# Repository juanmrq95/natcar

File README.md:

# Sp17_team3
Andrew Chan, Neeli Tummala, Juan Rodriguez

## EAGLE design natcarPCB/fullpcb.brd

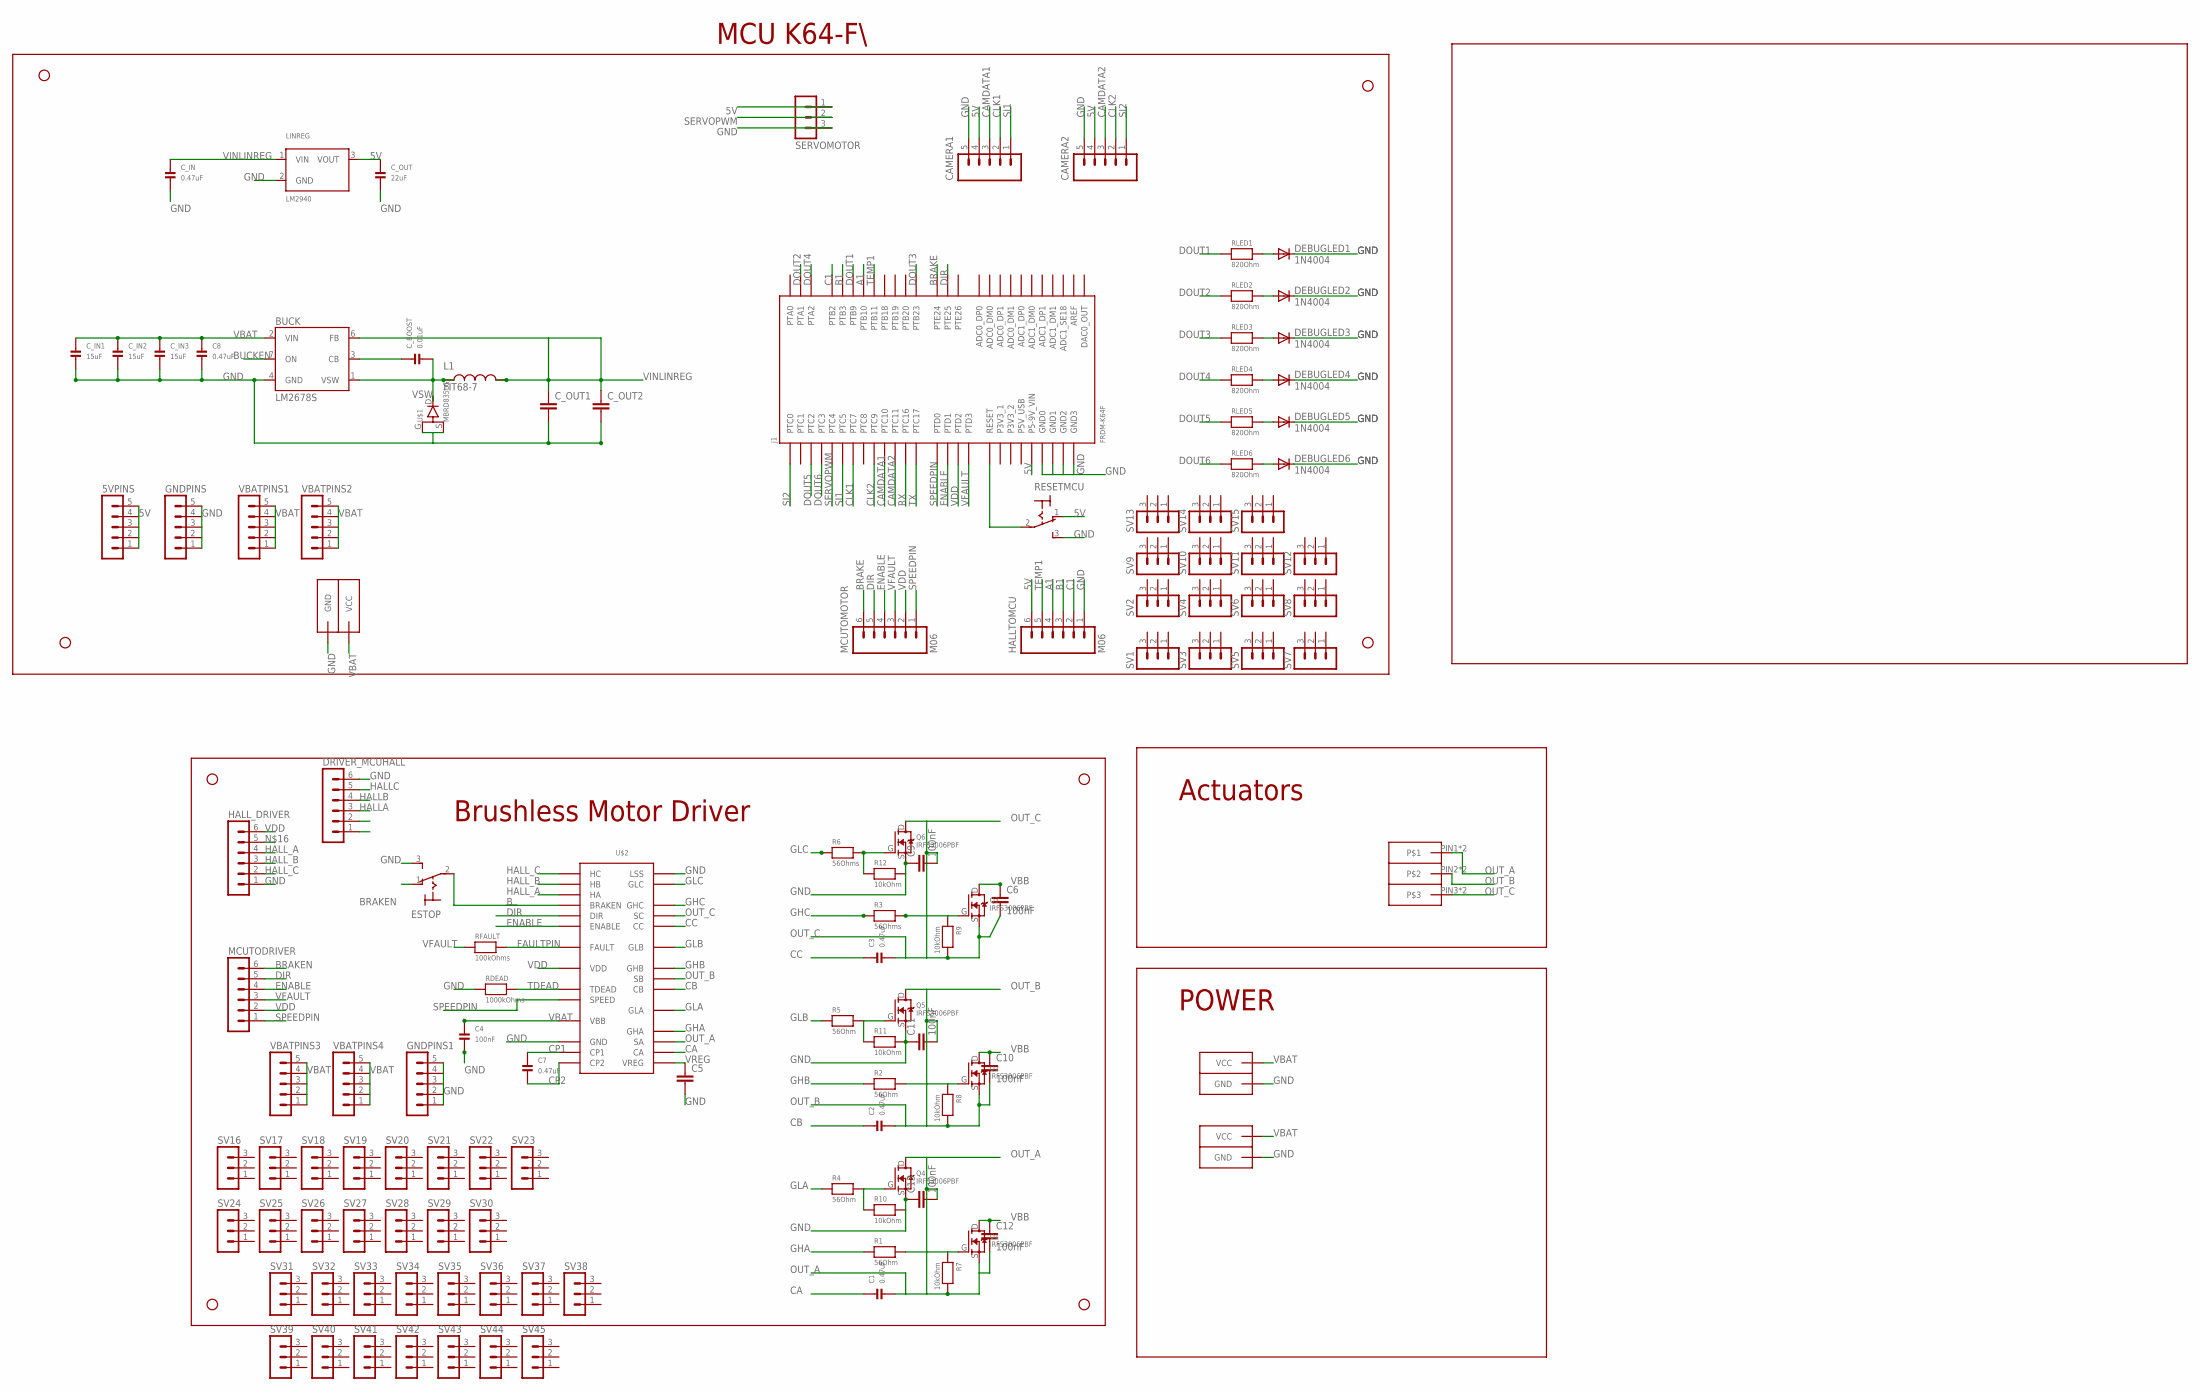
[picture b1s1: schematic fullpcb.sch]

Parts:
5VPINS: MA05-1
BOARD2BOARD: ANDERSON_PP_DOUBLEHORIZONTAL; ANDERSON_PP_DOUB_HORZ
BUCK: LM2678S; TO263-7
C1, C2, C3, C7, C8: 0.47uF; 0805
C4: 100nF; 0805
C5: C2,5-3; C2.5-3
C6, C9, C10, C11, C12, C13: 100nF; C2.5-3
CAMERA1, CAMERA2: M05PTH; 1X05
CONN1, CONN2: ANDERSON_PP_DOUBLEHORIZONTAL; ANDERSON_PP_DOUB_HORZ
CONN3: ANDERSON_PP_TRIPHORIZ; ANDERSON_PP_TRIP_HORZ
C_BOOST: 0.01uF; 0805
C_IN: 0.47uF; 0805
C_IN1, C_IN2, C_IN3: 15uF; 0805
C_OUT: 22uF; 0805
C_OUT1, C_OUT2: C2,5-3; C2.5-3
DEBUGLED1, DEBUGLED2, DEBUGLED3, DEBUGLED4, DEBUGLED5, DEBUGLED6: 1N4004; DO41-10
DRIVER_MCUHALL: MA06-1
ESTOP: M9040P
GNDPINS, GNDPINS1: MA05-1
HALLTOMCU: M06; 1X06-MTA
HALL_DRIVER: MA06-1
J1: FRDM-K64F
JP1, JP2, JP3, JP4, JP5, JP6, JP7, JP8: STAND-OFF
L1: FIT68-7
LINREG: LM2940; TO220V
MCUTODRIVER: MA06-1
MCUTOMOTOR: M06; 1X06-MTA
Q1, Q2, Q3, Q4, Q5, Q6: IRFS3006PBF
R1, R2, R4, R5: 56Ohm; 0805
R3, R6: 56Ohms; 0805
R7, R8, R9, R10, R11, R12: 10kOhm; 0805
RDEAD: 1000kOhms; 0805
RESETMCU: M9040P
RFAULT: 100kOhms; 0805
RLED1, RLED2, RLED3, RLED4, RLED5, RLED6: 820Ohm; 0805
SERVOMOTOR: MA03-1
SV1, SV2, SV3, SV4, SV5, SV6, SV7, SV8, SV9, SV10, SV11, SV12, SV13, SV14, SV15, SV16, SV17, SV18, SV19, SV20, SV21, SV22, SV23, SV24, SV25, SV26, SV27, SV28, SV29, SV30, SV31, SV32, SV33, SV34, SV35, SV36, SV37, SV38, SV39, SV40, SV41, SV42, SV43, SV44, SV45: MA03-1
U$1: MBRD835LG; DPACK_2
U$2: A4915SOCKET; DIL28-6
VBATPINS1, VBATPINS2, VBATPINS3, VBATPINS4: MA05-1

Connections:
5V: 5VPINS.1, 5VPINS.5, CAMERA1.4, CAMERA2.4, C_OUT.1, HALLTOMCU.6, J1.J3-16 (P5-9V_VIN), LINREG.3 (VOUT), RESETMCU.1 (O), SERVOMOTOR.1
A1: HALLTOMCU.4, J1.J4-6 (PTB10)
B1: HALLTOMCU.3, J1.J4-4 (PTB3)
BRAKE: J1.J2-20 (PTE24), MCUTOMOTOR.6
BRAKE1: ESTOP.2, U$2.25 (BRAKEN)
BRAKEN: ESTOP.1 (O), MCUTODRIVER.6
BUCKEN: BUCK.7 (ON)
C1: HALLTOMCU.2, J1.J4-2 (PTB2)
CA: C1.1, U$2.13 (CA)
CAMDATA1: CAMERA1.3, J1.J4-12 (PTC10)
CAMDATA2: CAMERA2.3, J1.J4-10 (PTC11)
CB: BUCK.3 (CB), C2.1, C_BOOST.1, U$2.9 (CB)
CC: C3.1, U$2.5 (CC)
CLK1: CAMERA1.2, J1.J1-13 (PTC7)
CLK2: CAMERA2.2, J1.J1-9 (PTC9)
CP1: C7.1, U$2.16 (CP1)
CP2: C7.2, U$2.15 (CP2)
DIR: J1.J2-18 (PTE25), MCUTODRIVER.5, MCUTOMOTOR.5, U$2.24 (DIR)
DOUT1: J1.J1-6 (PTB9), RLED1.1
DOUT2: J1.J1-8 (PTA1), RLED2.1
DOUT3: J1.J1-10 (PTB23), RLED3.1
DOUT4: J1.J1-12 (PTA2), RLED4.1
DOUT5: J1.J1-14 (PTC2), RLED5.1
DOUT6: J1.J1-16 (PTC3), RLED6.1
ENABLE: J1.J2-12 (PTD1), MCUTODRIVER.4, MCUTOMOTOR.4, U$2.23 (ENABLE)
FAULTPIN: RFAULT.2, U$2.22 (FAULT)
GHA: R1.1, U$2.11 (GHA)
GHB: R2.1, U$2.7 (GHB)
GHC: R3.1, U$2.3 (GHC)
GLA: R4.1, U$2.10 (GLA)
GLB: R5.1, U$2.6 (GLB)
GLC: R6.1, U$2.2 (GLC)
GND: BOARD2BOARD.PIN1 (GND), BOARD2BOARD.PIN1-LEAD (GND), BUCK.4 (GND), C4.2, C5.2, C8.2, C9.1, C11.1, C13.1, CAMERA1.5, CAMERA2.5, CONN1.PIN1 (GND), CONN1.PIN1-LEAD (GND), CONN2.PIN1 (GND), CONN2.PIN1-LEAD (GND), C_IN.2, C_IN1.2, C_IN2.2, C_IN3.2, C_OUT.2, C_OUT1.2, C_OUT2.2, DEBUGLED1.C, DEBUGLED2.C, DEBUGLED3.C, DEBUGLED4.C, DEBUGLED5.C, DEBUGLED6.C, DRIVER_MCUHALL.6, ESTOP.3 (S), GNDPINS.1, GNDPINS.5, GNDPINS1.1, GNDPINS1.5, HALLTOMCU.1, HALL_DRIVER.1, J1.J2-3 (GND0), J1.J2-14 (GND1), J1.J3-12 (GND2), J1.J3-14 (GND3), LINREG.2 (GND), Q4.S, Q5.S, Q6.S, R10.2, R11.2, R12.2, RESETMCU.3 (S), SERVOMOTOR.3, U$1.G (1), U$1.S (3), U$2.1 (LSS), U$2.17 (GND)
HALLA: DRIVER_MCUHALL.3
HALLB: DRIVER_MCUHALL.4
HALLC: DRIVER_MCUHALL.5
HALL_A: HALL_DRIVER.4, U$2.26 (HA)
HALL_B: HALL_DRIVER.3, U$2.27 (HB)
HALL_C: HALL_DRIVER.2, U$2.28 (HC)
unnamed: DEBUGLED2.A, RLED2.2
unnamed: DEBUGLED3.A, RLED3.2
unnamed: DEBUGLED4.A, RLED4.2
unnamed: DEBUGLED5.A, RLED5.2
unnamed: DEBUGLED6.A, RLED6.2
unnamed: J1.J3-6 (RESET), RESETMCU.2
unnamed: DEBUGLED1.A, RLED1.2
unnamed: Q1.G, R1.2, R7.1
unnamed: Q4.G, R4.2, R10.1
unnamed: Q2.G, R2.2, R8.1
unnamed: Q5.G, R5.2, R11.1
unnamed: Q6.G, R6.2, R12.1
unnamed: Q3.G, R3.2, R9.1
OUT_A: C1.2, C12.2, C13.2, CONN3.PIN1, CONN3.PIN1-LEAD, Q1.S, Q4.D, R7.2, U$2.12 (SA)
OUT_B: C2.2, C10.2, C11.2, CONN3.PIN2, CONN3.PIN2-LEAD, Q2.S, Q5.D, R8.2, U$2.8 (SB)
OUT_C: C3.2, C6.2, C9.2, CONN3.PIN3, CONN3.PIN3-LEAD, Q3.S, Q6.D, R9.2, U$2.4 (SC)
RX: J1.J1-2 (PTC16)
SERVOPWM: J1.J2-4 (PTC4), SERVOMOTOR.2
SI1: CAMERA1.1, J1.J1-15 (PTC5)
SI2: CAMERA2.1, J1.J1-11 (PTC0)
SPEEDPIN: J1.J2-6 (PTD0), MCUTODRIVER.1, MCUTOMOTOR.1, U$2.19 (SPEED)
TDEAD: U$2.20 (TDEAD)
TEMP1: HALLTOMCU.5, J1.J4-8 (PTB11)
TX: J1.J1-4 (PTC17)
VBAT: BOARD2BOARD.PIN2 (VCC), BOARD2BOARD.PIN2-LEAD (VCC), BUCK.2 (VIN), C4.1, C8.1, CONN1.PIN2 (VCC), CONN1.PIN2-LEAD (VCC), CONN2.PIN2 (VCC), CONN2.PIN2-LEAD (VCC), C_IN1.1, C_IN2.1, C_IN3.1, U$2.18 (VBB), VBATPINS1.1, VBATPINS1.5, VBATPINS2.1, VBATPINS2.5, VBATPINS3.1, VBATPINS3.5, VBATPINS4.1, VBATPINS4.5
VBB: C6.1, C10.1, C12.1, Q1.D, Q2.D, Q3.D
VDD: HALL_DRIVER.6, J1.J2-8 (PTD2), MCUTODRIVER.2, MCUTOMOTOR.2, U$2.21 (VDD)
VFAULT: J1.J2-10 (PTD3), MCUTODRIVER.3, MCUTOMOTOR.3, RFAULT.1
VINLINREG: BUCK.6 (FB), C_IN.1, C_OUT1.1, C_OUT2.1, L1.P$2, LINREG.1 (VIN)
VREG: C5.1, U$2.14 (VREG)
VSW: BUCK.1 (VSW), C_BOOST.2, L1.P$1

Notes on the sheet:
MCU K64-F\
Brushless Motor Driver
Actuators
POWER

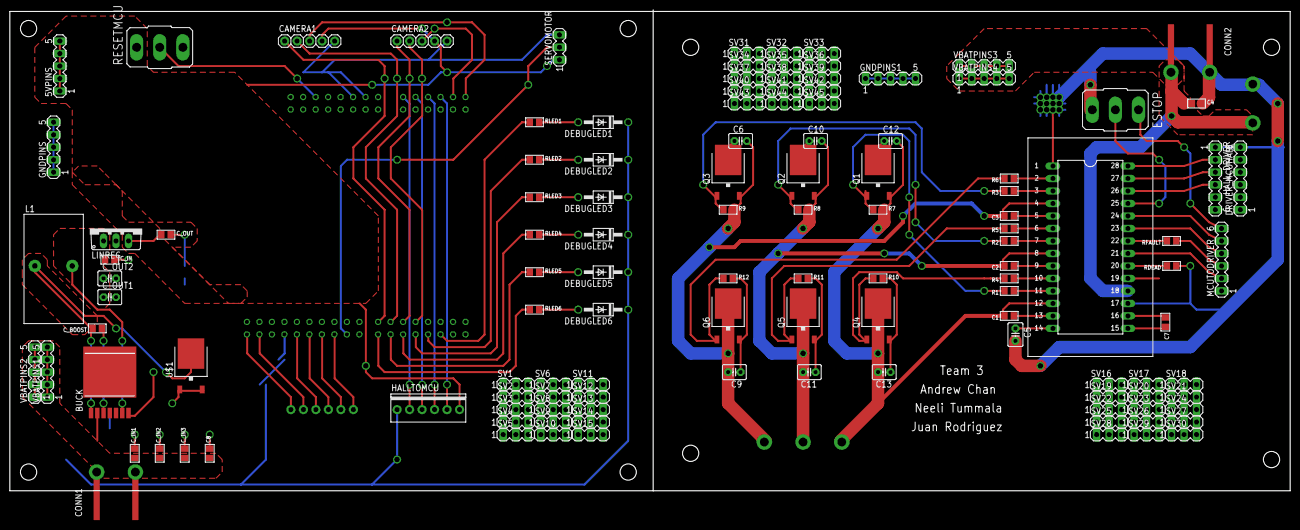
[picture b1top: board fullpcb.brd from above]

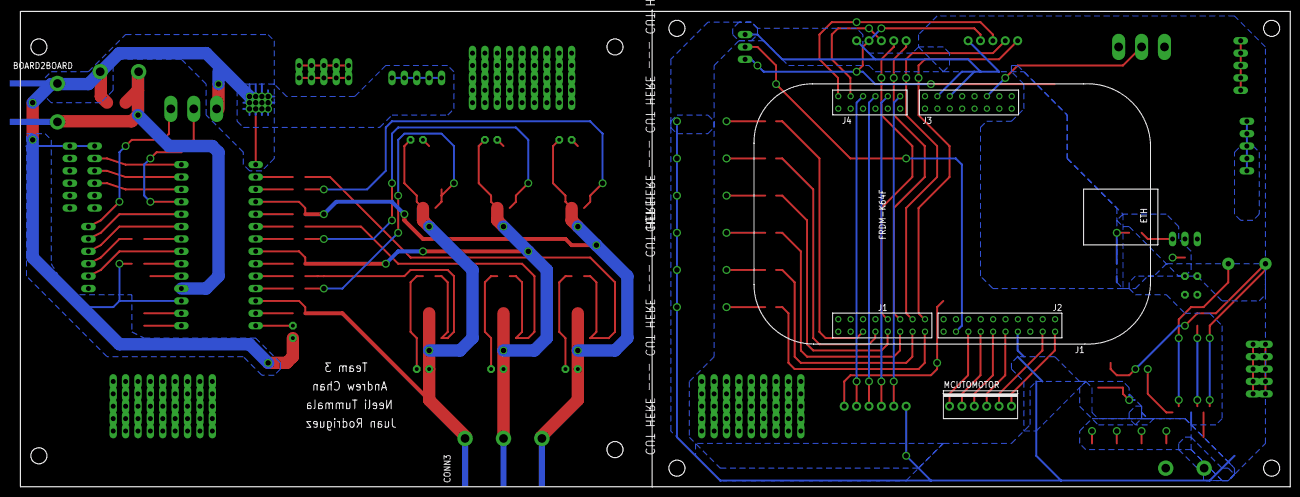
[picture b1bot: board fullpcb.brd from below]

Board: 2 copper layers, 260.3 x 97.8 mm, 133 parts (4 on the bottom side), 63 nets.

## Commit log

2018-02-01 added pcb

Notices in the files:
parts and their libraries:
microbuilder: This work is placed in the public domain, and may be freely used for commercial and non-commercial work with the following conditions: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
